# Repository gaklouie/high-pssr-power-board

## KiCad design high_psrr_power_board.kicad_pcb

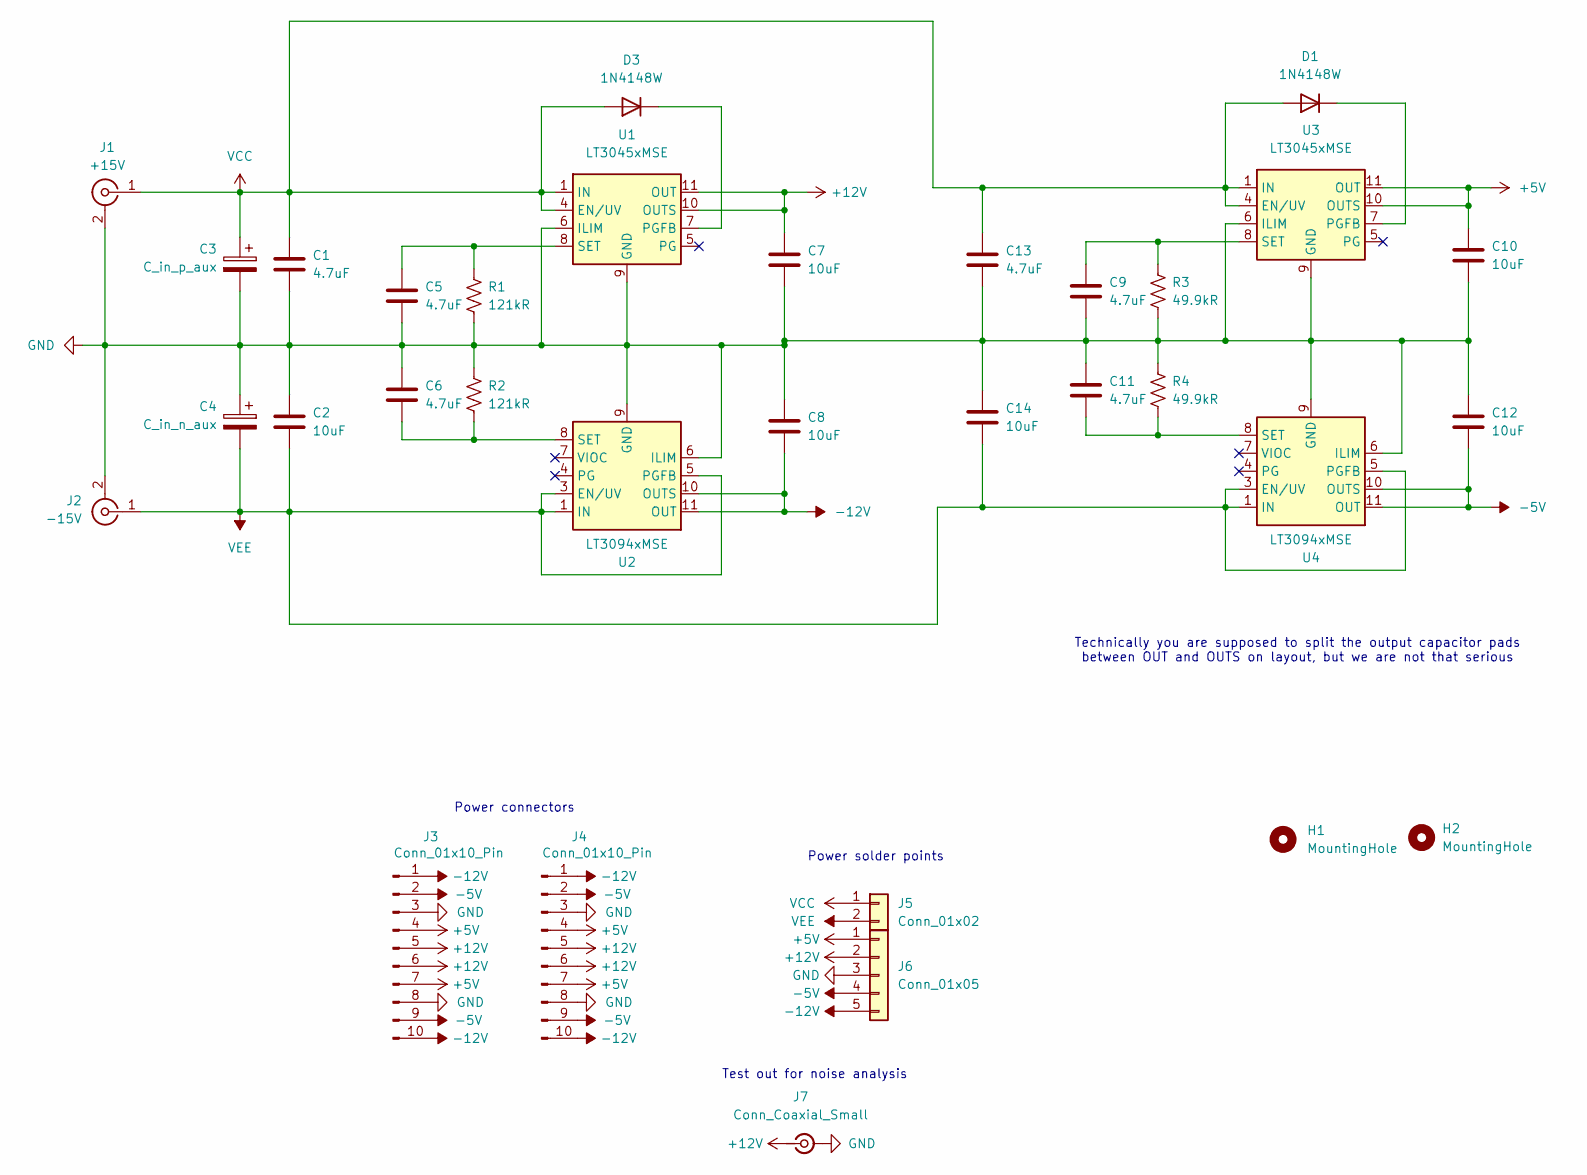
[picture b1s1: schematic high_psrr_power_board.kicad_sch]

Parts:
C1, C5, C6, C9, C11, C13: 4.7uF; C_1206_3216Metric; LCSC Part Number C126595
C2, C7, C8, C10, C12, C14: 10uF; C_1206_3216Metric; LCSC Part Number C126594
C3: C_in_p_aux; CP_Radial_D5.0mm_P2.00mm
C4: C_in_n_aux; CP_Radial_D5.0mm_P2.00mm
D1, D3: 1N4148W; D_SOD-123; LCSC Part Number C917030
H1, H2: MountingHole; MountingHole_2.7mm
J1: +15V; BNC_Amphenol_B6252HB-NPP3G-50_Horizontal
J2: -15V; BNC_Amphenol_B6252HB-NPP3G-50_Horizontal
J3, J4: Conn_01x10_Pin; JST_ZH_B10B-ZR_1x10_P1.50mm_Vertical
J5: Conn_01x02; SolderWire-1sqmm_1x02_P5.4mm_D1.4mm_OD2.7mm
J6: Conn_01x05; SolderWire-1sqmm_1x05_P5.4mm_D1.4mm_OD2.7mm
J7: Conn_Coaxial_Small; SMA_Amphenol_901-144_Vertical
R1, R2: 121kR; R_0603_1608Metric; LCSC Part Number C861095
R3, R4: 49.9kR; R_0603_1608Metric; LCSC Part Number C705780
U1, U3: LT3045xMSE; MSOP-12-1EP_3x4.039mm_P0.65mm_EP1.651x2.845mm; LCSC Part Number C666577
U2, U4: LT3094xMSE; MSOP-12-1EP_3x4.039mm_P0.65mm_EP1.651x2.845mm; LCSC Part Number C670494

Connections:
+5V: C10.1, J3.4, J3.7, J4.4, J4.7, J6.1, U3.10 (OUTS), U3.11 (OUT), U3.12 (OUT)
+12V: C7.1, J3.5, J3.6, J4.5, J4.6, J6.2, J7.1 (In), U1.10 (OUTS), U1.11 (OUT), U1.12 (OUT)
-5V: C12.2, J3.2, J3.9, J4.2, J4.9, J6.4, U4.10 (OUTS), U4.11 (OUT), U4.12 (OUT)
-12V: C8.2, J3.1, J3.10, J4.1, J4.10, J6.5, U2.10 (OUTS), U2.11 (OUT), U2.12 (OUT)
GND: C1.2, C2.1, C3.2, C4.1, C5.2, C6.1, C7.2, C8.1, C9.2, C10.2, C11.1, C12.1, C13.2, C14.1, J1.2 (Ext), J2.2 (Ext), J3.3, J3.8, J4.3, J4.8, J6.3, J7.2 (Ext), R1.2, R2.1, R3.2, R4.1, U1.6 (ILIM), U1.9 (GND), U1.13 (GND), U2.6 (ILIM), U2.9 (GND), U3.6 (ILIM), U3.9 (GND), U3.13 (GND), U4.6 (ILIM), U4.9 (GND)
unnamed: D1.1 (K), U3.7 (PGFB)
unnamed: D3.1 (K), U1.7 (PGFB)
unnamed: C5.1, R1.1, U1.8 (SET)
unnamed: C6.2, R2.2, U2.8 (SET)
unnamed: C9.1, R3.1, U3.8 (SET)
unnamed: C11.2, R4.2, U4.8 (SET)
VCC: C1.1, C3.1, C13.1, D1.2 (A), D3.2 (A), J1.1 (In), J5.1, U1.1 (IN), U1.2 (IN), U1.3 (IN), U1.4 (EN/UV), U3.1 (IN), U3.2 (IN), U3.3 (IN), U3.4 (EN/UV)
VEE: C2.2, C4.2, C14.2, J2.1 (In), J5.2, U2.1 (IN), U2.2 (IN), U2.3 (EN/UV), U2.5 (PGFB), U2.13 (IN), U4.1 (IN), U4.2 (IN), U4.3 (EN/UV), U4.5 (PGFB), U4.13 (IN)

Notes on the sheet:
Power solder points
Test out for noise analysis
Technically you are supposed to split the output capacitor pads between OUT and OUTS on layout, but we are not that serious
Power connectors

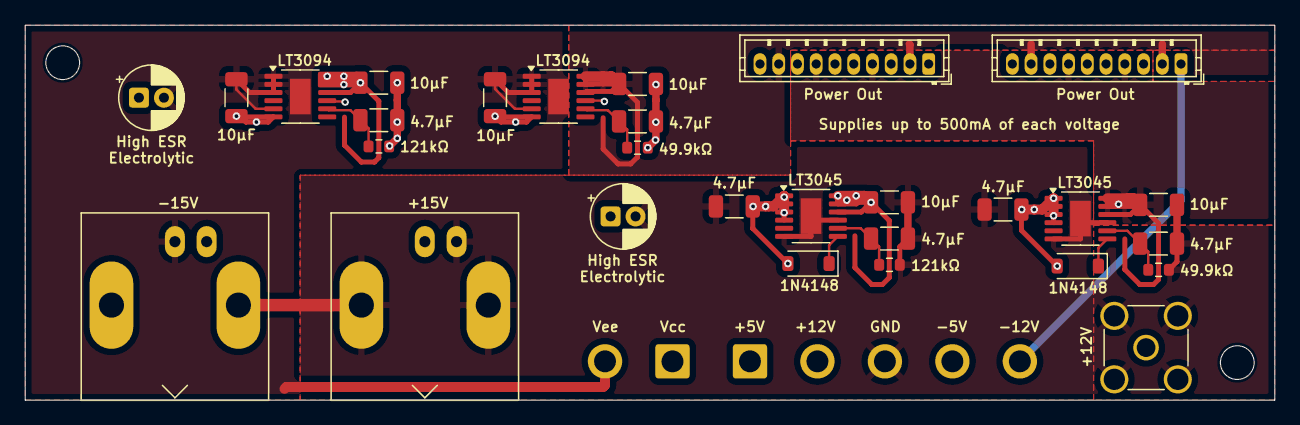
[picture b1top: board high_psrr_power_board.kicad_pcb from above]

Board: 4 copper layers, 100.0 x 30.0 mm, 33 parts (0 on the bottom side), 13 nets.

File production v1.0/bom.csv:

Designator,Footprint,Quantity,Value,LCSC Part #
"C1, C11, C13, C5, C6, C9",1206,6,4.7uF,C126595
"C10, C12, C14, C2, C7, C8",1206,6,10uF,C126594
"D1, D3",D_SOD-123,2,1N4148W,C917030
"R1, R2",0603,2,121kR,C861095
"R3, R4",0603,2,49.9kR,C705780
"U1, U3",MSOP-12-1EP_3x4.039mm_P0.65mm_EP1.651x2.845mm,2,LT3045xMSE,C666577
"U2, U4",MSOP-12-1EP_3x4.039mm_P0.65mm_EP1.651x2.845mm,2,LT3094xMSE,C670494
